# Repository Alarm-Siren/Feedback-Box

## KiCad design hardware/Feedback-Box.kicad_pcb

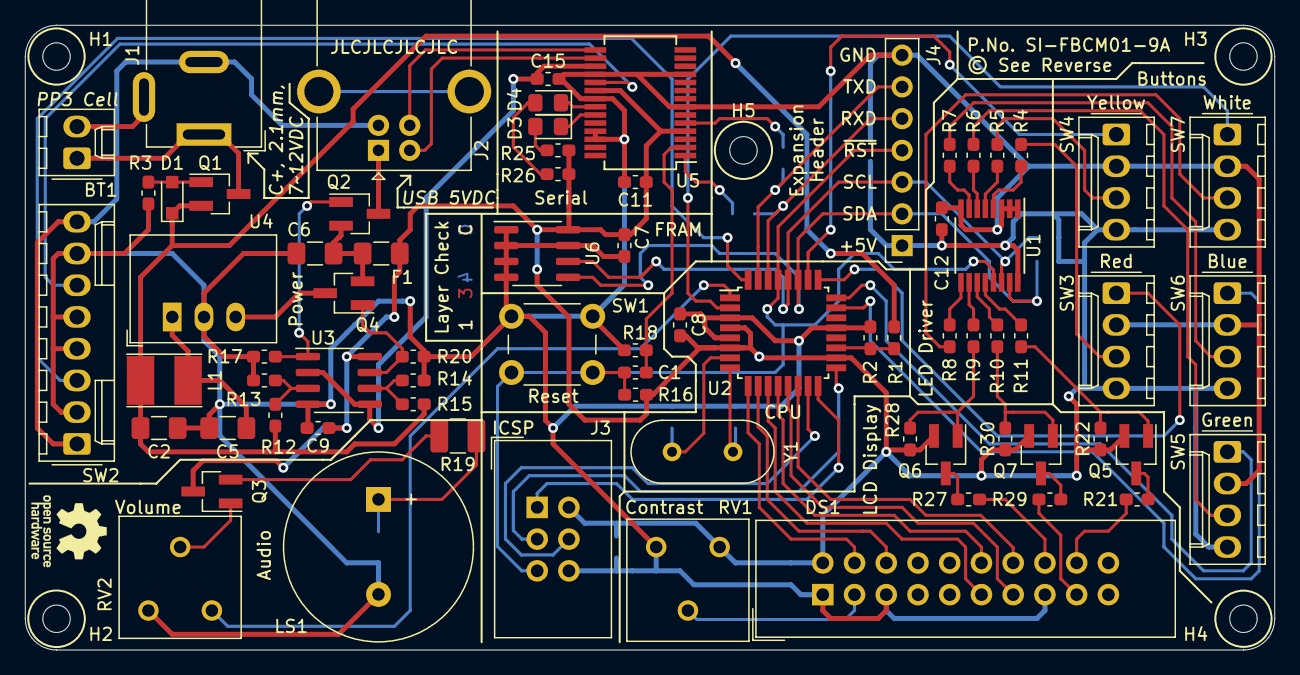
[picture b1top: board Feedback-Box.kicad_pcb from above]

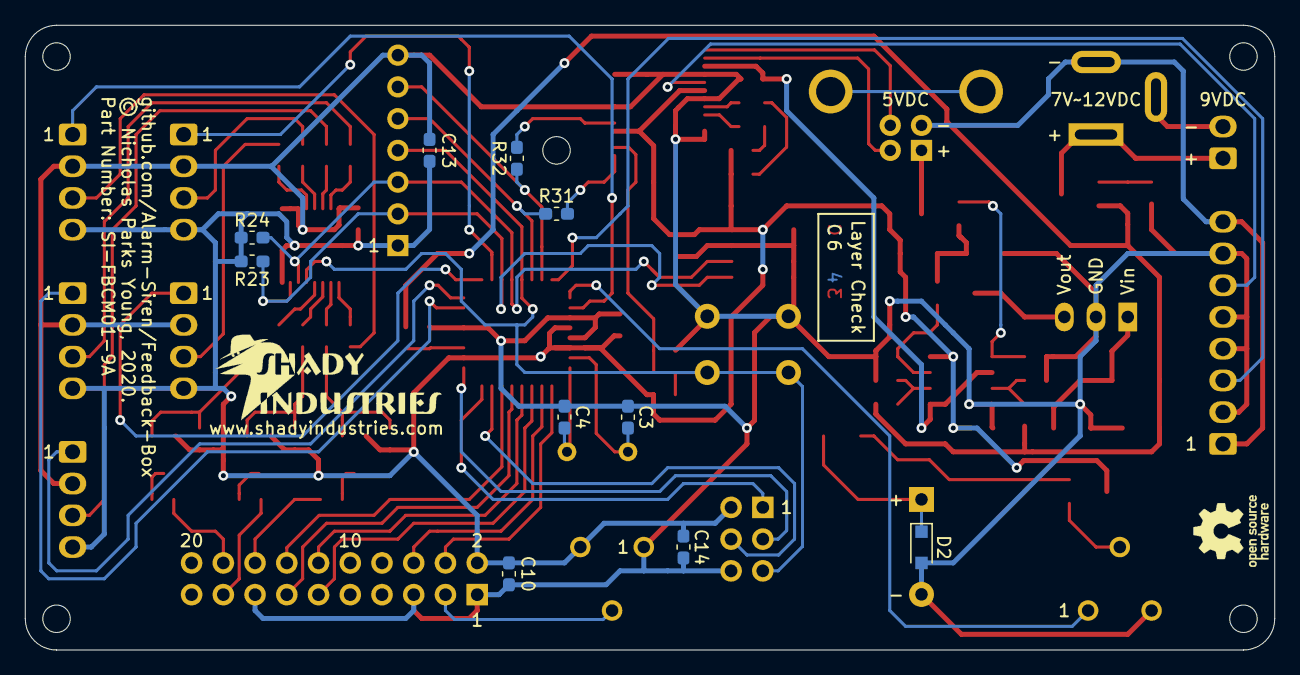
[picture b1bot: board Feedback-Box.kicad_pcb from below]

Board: 2 copper layers, 100.0 x 50.0 mm, 91 parts (12 on the bottom side), 76 nets.

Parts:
BT1: BX0023; Molex_KK-254_AE-6410-02A_1x02_P2.54mm_Vertical
C1, C7, C8, C9, C10, C11, C12, C13, C14, C15: 100n; C_0603_1608Metric_Pad1.05x0.95mm_HandSolder
C2, C6: 10u; C_1206_3216Metric_Pad1.42x1.75mm_HandSolder
C3, C4: 22p; C_0603_1608Metric_Pad1.05x0.95mm_HandSolder
C5: 4.7u; C_1206_3216Metric_Pad1.42x1.75mm_HandSolder
D1: MM3Z7V5ST1G; D_SOD-323_HandSoldering
D2: SS16HE; D_SOD-323_HandSoldering
D3: LTST-C171KRKT; LED_0805_2012Metric_Pad1.15x1.40mm_HandSolder
D4: LTSTS-C171KGKT; LED_0805_2012Metric_Pad1.15x1.40mm_HandSolder
DS1: NHD-0216K1Z-FS(RGB)-FBW-REV1; IDC-Header_2x10_P2.54mm_Vertical
F1: 0ZCJ0025AF2E; Fuse_1206_3216Metric_Pad1.42x1.75mm_HandSolder
G1: LOGO; SI-Logo-W20.3mm_H8.4mm
G2, G3: OSHW-Logo_5.7x6mm_SilkScreen
H1, H2, H3, H4, H5: MountingHole_2.2mm_M2
J1: 694106301002; BarrelJack_Wuerth_6941xx301002
J2: UJ2-BH-1-TH; USB_B_OST_USB-B1HSxx_Horizontal
J3: T821106A1S100CEU; IDC-Header_2x03_P2.54mm_Vertical
J4: SSW-107-01-T-S; PinSocket_1x07_P2.54mm_Vertical
L1: 12u; L_Taiyo-Yuden_NR-40xx_HandSoldering
LS1: CVS-1508; Buzzer_15x7.5RM7.6
Q1, Q2, Q4, Q5, Q6, Q7: FDN340P; SOT-23_Handsoldering
Q3: MMBT2222ALT1G; SOT-23_Handsoldering
R1: 8.2k; R_0603_1608Metric_Pad1.05x0.95mm_HandSolder
R2: 4.7k; R_0603_1608Metric_Pad1.05x0.95mm_HandSolder
R3, R13, R15: 100k; R_0603_1608Metric_Pad1.05x0.95mm_HandSolder
R4, R5, R6, R7, R8, R21, R29: 120; R_0603_1608Metric_Pad1.05x0.95mm_HandSolder
R9, R10, R11: 0; R_0603_1608Metric_Pad1.05x0.95mm_HandSolder
R12, R17, R20, R22, R28, R30: 68k; R_0603_1608Metric_Pad1.05x0.95mm_HandSolder
R14: 82k; R_0603_1608Metric_Pad1.05x0.95mm_HandSolder
R16: 10k; R_0603_1608Metric_Pad1.05x0.95mm_HandSolder
R18, R25, R26, R31, R32: 1k; R_0603_1608Metric_Pad1.05x0.95mm_HandSolder
R19: 62; R_1210_3225Metric_Pad1.42x2.65mm_HandSolder
R23, R24: 3.3k; R_0603_1608Metric_Pad1.05x0.95mm_HandSolder
R27: 150; R_0603_1608Metric_Pad1.05x0.95mm_HandSolder
RV1, RV2: 10k; Potentiometer_Bourns_3386F_Vertical
SW1: B3W-1000; SW_PUSH_6mm
SW2: Y200AA2C203NQ; Molex_KK-254_AE-6410-08A_1x08_P2.54mm_Vertical
SW3: EG Starts Red; Molex_KK-254_AE-6410-04A_1x04_P2.54mm_Vertical
SW4: EG Starts Yellow; Molex_KK-254_AE-6410-04A_1x04_P2.54mm_Vertical
SW5: EG Starts Green; Molex_KK-254_AE-6410-04A_1x04_P2.54mm_Vertical
SW6: EG Starts Blue; Molex_KK-254_AE-6410-04A_1x04_P2.54mm_Vertical
SW7: EG Starts White; Molex_KK-254_AE-6410-04A_1x04_P2.54mm_Vertical
U1: TLC59208FIPWR; TSSOP-16_4.4x5mm_P0.65mm
U2: ATmega328P-AU; TQFP-32_7x7mm_P0.8mm
U3: LMV358IDR; SOIC-8_3.9x4.9mm_P1.27mm
U4: R-78E5.0-0.5; Converter_DCDC_RECOM_R-78E-0.5_THT
U5: FT232RL; SSOP-28_5.3x10.2mm_P0.65mm
U6: FM24C16B; SOIC-8_3.9x4.9mm_P1.27mm
Y1: 16MHz; Crystal_HC49-4H_Vertical

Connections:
+3V3: C15.1, U3.2, U3.5, U5.17
+5V: C7.1, C8.1, C9.1, C10.1, C11.1, C12.1, C13.1, C14.1, DS1.2, F1.1, J3.2, J4.1, Q3.3, Q5.2, Q6.2, Q7.2, R16.2, R22.2, R23.2, R24.2, R25.1, R26.1, R28.2, R30.2, RV1.3, SW3.4, SW4.4, SW5.4, SW6.4, SW7.4, U1.16, U2.4, U2.6, U2.18, U3.8, U5.4, U5.20, U6.8
/MISO: J3.1, U2.16
/MOSI: J3.4, U2.15
/SCLK: J3.3, U2.17
/XTAL1: C3.2, U2.7, Y1.1
/XTAL2: C4.2, U2.8, Y1.2
/~RXLED: D4.1, U5.22
/~TXLED: D3.1, U5.23
BAT: C2.1, D1.1, L1.1, Q1.2, R1.2, R12.2, R14.2
BTN1: SW3.1, U2.25
BTN2: SW4.1, U2.26
BTN3: SW5.1, U2.24
BTN4: SW6.1, U2.23
BTN5: SW7.1, U2.2
GND: C2.2, C3.1, C4.1, C5.2, C6.2, C7.2, C8.2, C9.2, C10.2, C11.2, C12.2, C13.2, C14.2, C15.2, D2.2, DS1.1, DS1.5, DS1.15, J3.6, J4.7, LS1.2, R2.1, R3.1, R13.1, R15.1, R17.1, R18.1, R20.1, RV1.1, RV2.3, SW1.2, SW2.2, SW2.4, SW2.5, SW2.7, SW3.2, SW4.2, SW5.2, SW6.2, SW7.2, U1.1, U1.2, U1.3, U1.8, U2.3, U2.5, U2.21, U3.4, U4.2, U5.7, U5.11, U5.18, U5.21, U5.25, U5.26, U6.1, U6.2, U6.3, U6.4, U6.7
GNDS: J1.2, J2.4, SW2.1, SW2.8
LCD_D4: DS1.11, U2.11
LCD_D5: DS1.12, U2.12
LCD_D6: DS1.13, U2.13
LCD_D7: DS1.14, U2.14
LCD_E: DS1.6, U2.10
LCD_RS: DS1.4, U2.9
LED1: R4.1, SW3.3
LED2: R5.1, SW4.3
LED3: R6.1, SW5.3
LED4: R7.1, SW6.3
LED5: R8.1, SW7.3
unnamed: BT1.1, J1.1, Q1.3
unnamed: BT1.2, J1.3
unnamed: C5.1, L1.2, U4.1
unnamed: C6.1, F1.2, Q2.2, Q4.2
unnamed: D1.2, Q1.1, R3.2
unnamed: D2.1, LS1.1, R19.1
unnamed: D3.2, R25.2
unnamed: D4.2, R26.2
unnamed: DS1.3, RV1.2
unnamed: J2.1, Q2.3
unnamed: Q2.1, R17.2, U3.1
unnamed: Q3.1, RV2.2
unnamed: Q3.2, R19.2
unnamed: Q4.1, R20.2, U3.7
unnamed: Q4.3, U4.3
unnamed: Q5.3, R21.1
unnamed: Q6.3, R27.1
unnamed: Q7.3, R29.1
unnamed: R1.1, R2.2, U2.19
unnamed: R4.2, U1.4
unnamed: R5.2, U1.5
unnamed: R6.2, U1.6
unnamed: R7.2, U1.7
unnamed: R8.2, U1.9
unnamed: R9.2, U1.10
unnamed: R10.2, U1.11
unnamed: R11.2, U1.12
unnamed: R12.1, R13.2, U3.3
unnamed: R14.1, R15.2, U3.6
unnamed: R31.2, U5.1
unnamed: R32.2, U5.5
PROG~EN: SW2.3, U2.32
RXD: J4.5, R31.1, U2.30
SCL: J4.3, R24.1, U1.14, U2.28, U6.6
SCR_B+: DS1.18, R21.2
SCR_B-: Q5.1, R11.1, R22.1
SCR_G+: DS1.17, R29.2
SCR_G-: Q7.1, R10.1, R30.1
SCR_R+: DS1.16, R27.2
SCR_R-: Q6.1, R9.1, R28.1
SDA: J4.2, R23.1, U1.15, U2.27, U6.5
SPK: RV2.1, U2.1
TXD: J4.6, R32.1, U2.31
USBD+: J2.3, U5.15
USBD-: J2.2, U5.16
USB~RST: SW2.6, U5.19
~DTR: C1.1, R18.2, U5.2
~RST: C1.2, J3.5, J4.4, R16.1, SW1.1, U1.13, U2.29

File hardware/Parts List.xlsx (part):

Reference | Manufacturer | Mft's Part Number | Qty/unit | Total Qty | Price/each (£) | Subtotal (£) | Mouser Part No | Farnell Part No | Misc. Part Link | Footprint | Description
BT1 | Bulgin | BX0023 | 1 | 5 | 4.4800000000000004 | 22.400000000000002 | 122-BX0023 | 1184193 |  | n/a | PP3 (9V) battery holder, panel-mount, black, Flying Leads
BT1a | Molex | 22292021 | 1 | 5 | 0.32800000000000001 | 1.6400000000000001 | 538-22-29-2021 | 1360130 |  | Connector_Molex:Molex_KK-254_AE-6410-02A_1x02_P2.54mm_Vertical | Molex KK 254 Series, 2pin header, Wire-to-board, THT
BT1b | Molex | 22013027 | 1 | 5 | 6.4199999999999993E-2 | 0.32099999999999995 | 538-22-01-3027 | 1462825 |  | n/a | Molex KK Connector Housing 2pin w/Mating flange & polarizing ribs
BT1c, SW2c | Molex | 08520123 | 44 | 220 | 1.8100000000000002E-2 | 3.9820000000000002 | 538-08-52-0101-CT | 2888993 |  | n/a | Molex KK Crimp Contacts, 30-22AWG, Phospher Bronze, Cut Strip
C1, C7-C15 | Wurth Elektronik | 885012206071 | 10 | 50 | 2.8000000000000001E-2 | 1.4000000000000001 | 710-885012206071 | 2495173 |  | Capacitor_SMD:C_0603_1608Metric_Pad1.05x0.95mm_HandSolder | Capacitor MLCC 100nF, X7R, 25V, +/-10%, SMD 0603
C2, C6 | Taiyo Yuden | UMK316BBJ106KL-T | 2 | 10 | 0.13900000000000001 | 1.3900000000000001 | 963-UMK316BBJ106KL-T |  |  | Capacitor_SMD:C_1206_3216Metric_Pad1.42x1.75mm_HandSolder | Capacitor MLCC 10uF, X5R, 50V, +/-10%, SMD 1206
C3, C4 | AVX | 06035C220JAT2A | 2 | 10 | 6.6000000000000003E-2 | 0.66 | 581-06035C220JAT2A | 2332643 |  | Capacitor_SMD:C_0603_1608Metric_Pad1.05x0.95mm_HandSolder | Capacitor MLCC 22pF, X7R, 50V, +/-5%, SMD 0603
C5 | Taiyo Yuden | UMK316AB7475KL-T | 1 | 5 | 0.24 | 1.2 | 963-UMK316AB7475KL-T |  |  | Capacitor_SMD:C_1206_3216Metric_Pad1.42x1.75mm_HandSolder | Capacitor MLCC 4.7uF, X7R, 50V, +/-10%, SMD 1206
D1 | ON Semiconductor | MM3Z7V5ST1G | 1 | 5 | 9.2999999999999999E-2 | 0.46499999999999997 | 863-MM3Z7V5ST1G | 2441322 |  | Diode_SMD:D_SOD-323_HandSoldering | Single Zener Diode, 7.5V, 300mW, SMD SOD-323
D2 | ON Semiconductor / Fairchild | SS16HE | 1 | 5 | 7.6999999999999999E-2 | 0.38500000000000001 | 512-SS16HE | 2822565 |  | Diode_SMD:D_SOD-323_HandSoldering | Schottky Rectifier Diode, Vmax=60V, Imax=1A, Vf=680mV, SMD SOD-323
D3 | Lite-On | LTST-C171KRKT | 1 | 5 | 0.217 | 1.085 | 859-LTST-C171KRKT |  |  | LED_SMD:LED_0805_2012Metric_Pad1.15x1.40mm_HandSolder | Standard Red LED, 55mCD, SMD 0805
D4 | Lite-On | LTST-C171KGKT | 1 | 5 | 0.217 | 1.085 | 859-LTST-C171KGKT |  |  | LED_SMD:LED_0805_2012Metric_Pad1.15x1.40mm_HandSolder | Standard Green LED, 55mCD, SMD 0805
DS1 | Newhaven Displays | NHD-0216K1Z-FS(RGB)-FBW-REV1 | 1 | 5 | 10.55 | 52.75 | 763-0216K1Z-FS-FBWR1 |  |  | n/a | Character LCD 16x2, RGB Backlight, Parallel access, THT
DS1a | Amphenol | T821120A1S100CEU | 1 | 5 | 0.248 | 1.24 |  | 2215309 |  | Connector_IDC:IDC-Header_2x10_P2.54mm_Vertical | IDC Socket 2.54mm pitch, 2x10, Vertical, THT
DS1b | Amphenol | T812120A100CEU | 1 | 5 | 0.23 | 1.1500000000000001 |  | 2215236 |  | n/a | IDC Plug 2.54mm pitch, 2x10, Vertical
DS1c, SW2a | Molex | 22272081 | 2 | 10 | 0.33700000000000002 | 3.37 | 538-22-27-2081 | 9731180 |  | Connector_Molex:Molex_KK-254_AE-6410-08A_1x08_P2.54mm_Vertical | Molex KK 254 Series, 8pin header, Wire-to-board, THT
DS1d, SW2b | Molex | 22013087 | 2 | 10 | 0.20599999999999999 | 2.06 | 538-22-01-3087 | 2396394 |  | n/a | Molex KK Connector Housing 8pin w/Mating flange & polarizing ribs
DS1e | Molex | 22272061 | 1 | 5 | 0.33 | 1.6500000000000001 | 538-22-27-2061 | 9731172 |  | n/a | Molex KK 254 Series, 6pin header, Wire-to-board, THT
DS1f | Molex | 22013067 | 1 | 5 | 0.192 | 0.96 | 538-22-01-3067 | 1654529 |  | n/a | Molex KK Connector Housing 6pin w/Mating flange & polarizing ribs
F1 | Bel Fuse | 0ZCJ0025AF2E | 1 | 5 | 8.5000000000000006E-2 | 0.42500000000000004 | 530-0ZCJ0025AF2E | 2834884 |  | Fuse:Fuse_1206_3216Metric_Pad1.42x1.75mm_HandSolder | PTC Resettable Fuse, Hold 250mA, Trip 500mA, 24VDC, SMD 1206
J1 | Wurth Elektronik | 694106301002 | 1 | 5 | 0.70099999999999996 | 3.5049999999999999 | 710-694106301002 | 2472149 |  | Connector_BarrelJack:BarrelJack_Wuerth_6941xx301002 | Barrel Jack Socket, ID 2.1mm, OD 5.5mm, THT
J2 | CUI Devices | UJ2-BH-1-TH | 1 | 5 | 0.41799999999999998 | 2.09 | 490-UJ2-BH-1-TH |  |  | Connector_USB:USB_B_OST_USB-B1HSxx_Horizontal | USB-B Socket, THT
J3 | Amphenol | T821106A1S100CEU | 1 | 5 | 0.19900000000000001 | 0.99500000000000011 |  | 2215302 |  | Connector_IDC:IDC-Header_2x03_P2.54mm_Vertical | IDC Socket 2.54mm pitch, 2x3, Vertical, THT
J4 | Samtec | SSW-107-01-T-S | 1 | 5 | 0.73499999999999999 | 3.6749999999999998 | 200-SSW10701TS | 2667434 |  | Connector_PinSocket_2.54mm:PinSocket_1x07_P2.54mm_Vertical | 1x07 2.54mm Square Header Recepticle, Vertical, THT
L1 | RECOM | RLS-126 | 1 | 5 | 0.46800000000000003 | 2.3400000000000003 | 919-RLS-126 |  |  | Inductor_SMD:L_Taiyo-Yuden_NR-40xx_HandSoldering | 12uH 0.8A Fixed Inductor, SMD
LS1 | CUI Devices | CVS-1508 | 1 | 5 | 2.29 | 11.45 | 490-CVS-1508 |  |  | Buzzer_Beeper:Buzzer_15x7.5RM7.6 | Loudspeaker, 300mW 8R, D15mm, THT
Q1-Q2, Q4-Q7 | ON Semiconductor / Fairchild | FDN340P | 6 | 30 | 0.25600000000000001 | 7.68 | 512-FDN340P | 9846310 |  | Package_TO_SOT_SMD:SOT-23_Handsoldering | Mosfet Transistor, P-Channel, 2A, 20V, 0.06R, SMD SOT-23
Q3 | ON Semiconductor | MMBT2222ALT1G | 1 | 5 | 0.10100000000000001 | 0.505 | 863-MMBT2222ALT1G | 1459098 |  | Package_TO_SOT_SMD:SOT-23_Handsoldering | Bipolar Transistor, NPN, 40V, 300MHz, 225mW, 600mA, SMD SOT-23
R1 | Yageo | RC0603FR-078K2L | 1 | 5 | 1.4E-2 | 7.0000000000000007E-2 | 603-RC0603FR-078K2L | 9238590 |  | Resistor_SMD:R_0603_1608Metric_Pad1.05x0.95mm_HandSolder | Resistor 8.2kR, 100mW, 75V, +/-1%, SMD 0603
R12, R17, R20, R22, R28, R30 | Yageo | RC0603FR-0768KL | 6 | 30 | 1.4E-2 | 0.42 | 603-RC0603FR-0768KL | 9238700 |  | Resistor_SMD:R_0603_1608Metric_Pad1.05x0.95mm_HandSolder | Resistor 68kR, 100mW, 75V, +/-1%, SMD 0603
R14 | Yageo | RC0603FR-0782KL | 1 | 5 | 1.4E-2 | 7.0000000000000007E-2 | 603-RC0603FR-0782KL | 9238719 |  | Resistor_SMD:R_0603_1608Metric_Pad1.05x0.95mm_HandSolder | Resistor 82kR, 100mW, 75V, +/-1%, SMD 0603
R16 | Yageo | RC0603FR-0710KL | 1 | 5 | 1.4E-2 | 7.0000000000000007E-2 | 603-RC0603FR-0710KL | 9238603 |  | Resistor_SMD:R_0603_1608Metric_Pad1.05x0.95mm_HandSolder | Resistor 10kR, 100mW, 75V, +/-1%, SMD 0603
R18, R25-R26, R31-R32 | Yageo | RC0603FR-071KL | 5 | 25 | 1.4E-2 | 0.35000000000000003 | 603-RC0603FR-071KL | 9238484 |  | Resistor_SMD:R_0603_1608Metric_Pad1.05x0.95mm_HandSolder | Resistor 1kR, 100mW, 75V, +/-1%, SMD 0603
R19 | Yageo | RC1210FR-0762RL | 1 | 5 | 0.122 | 0.61 | 603-RC1210FR-0762RL |  |  | Resistor_SMD:R_1210_3225Metric_Pad1.42x2.65mm_HandSolder | Resistor 62R, 500mW, 75V, +/-1%, SMD 1210
R2 | Yageo | RC0603FR-074K7L | 1 | 5 | 1.4E-2 | 7.0000000000000007E-2 | 603-RC0603FR-074K7L | 9238565 |  | Resistor_SMD:R_0603_1608Metric_Pad1.05x0.95mm_HandSolder | Resistor 4.7kR, 100mW, 75V, +/-1%, SMD 0603
R23, R24 | Yageo | RC0603FR-073K3L | 2 | 10 | 1.4E-2 | 0.14000000000000001 | 603-RC0603FR-073K3L | 9238549 |  | Resistor_SMD:R_0603_1608Metric_Pad1.05x0.95mm_HandSolder | Resistor 3.3kR, 100mW, 75V, +/-1%, SMD 0603
R27 | Yageo | RC0603FR-07150RL | 1 | 5 | 1.4E-2 | 7.0000000000000007E-2 | 603-RC0603FR-07150RL | 9238387 |  | Resistor_SMD:R_0603_1608Metric_Pad1.05x0.95mm_HandSolder | Resistor 150R, 100mW, 75V, +/-1%, SMD 0603
R3, R13, R15 | Yageo | RC0603FR-07100KL | 3 | 15 | 1.4E-2 | 0.21 | 603-RC0603FR-07100KL | 9238727 |  | Resistor_SMD:R_0603_1608Metric_Pad1.05x0.95mm_HandSolder | Resistor 100kR, 100mW, 75V, +/-1%, SMD 0603
R4-R8, R21, R29 | Yageo | RC0603FR-07120RL | 7 | 35 | 1.4E-2 | 0.49 | 603-RC0603FR-07120RL | 9238379 |  | Resistor_SMD:R_0603_1608Metric_Pad1.05x0.95mm_HandSolder | Resistor 120R, 100mW, 75V, +/-1%, SMD 0603
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
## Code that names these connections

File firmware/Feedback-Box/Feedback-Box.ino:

#include <Wire.h>
#include <LiquidCrystal.h>

const byte LED_ADDR = 0x20;
const byte LED_PWM_VAL = 0xFF;
const byte LED_PWM_OFF = 0x00;

const byte LCD_RS = 5;
const byte LCD_EN = 6;
const byte LCD_D4 = 7;
const byte LCD_D5 = 8;
const byte LCD_D6 = 9;
const byte LCD_D7 = 10;

const byte BUTTON_RED = A2;
const byte BUTTON_YEL = A3;
const byte BUTTON_GRN = A1;
const byte BUTTON_BLU = A0;
const byte BUTTON_WHT = 4;
const byte PROG_EN = 2;

const byte BAT_MON = A6;

const byte FRAM_ADDR = 0x50;

const byte SPK_OUT = 3;
const unsigned int NOTE_SUSTAIN = 75;
const unsigned int NOTE_A5 = 880;
const unsigned int NOTE_B5 = 988;
const unsigned int NOTE_C5 = 523;
const unsigned int NOTE_D5 = 587;
const unsigned int NOTE_D5S = 622;
const unsigned int NOTE_E5 = 659;
const unsigned int NOTE_G4 = 392;
const unsigned int NOTE_C4 = 256;
const unsigned int NOTE_D3S = 155;
const unsigned int NOTE_A4S = 459;
const unsigned int NOTE_C5S = 554;


LiquidCrystal lcd(LCD_RS, LCD_EN, LCD_D4, LCD_D5, LCD_D6, LCD_D7);

void setup() {
  // put your setup code here, to run once:
  Wire.begin();

    Wire.beginTransmission(LED_ADDR);
    Wire.write(0x80); // Control: Auto-Increment on All Registers
    Wire.write(0x80); // 00h: MODE1
    Wire.write(0x0b); // 01h: MODE2
    Wire.write(0x00); // 02h: PWM0
    Wire.write(0x00); // 03h: PWM1
    Wire.write(0x00); // 04h: PWM2
    Wire.write(0x00); // 05h: PWM3
    Wire.write(0x00); // 06h: PWM4
    Wire.write(0x00); // 07h: PWM5
    Wire.write(0x00); // 08h: PWM6
    Wire.write(0x00); // 09h: PWM7
    Wire.write(0xFF); // 0Ah: GRPPWM
    Wire.write(0x00); // 0Bh: GRPFREQ
    Wire.write(0xAA); // 0Ch: LEDOUT0
    Wire.write(0xAA); // 0Dh: LEDOUT1
    Wire.write(0x92); // 0Eh: SUBADR1
    Wire.write(0x94); // 0Fh: SUBADR2
    Wire.write(0x98); // 10h: SUBADR3
    Wire.write(0xD0); // 11h: ALLCALLADR
    Wire.endTransmission();

  lcd.begin(16, 2);
  lcd.print("SIFBCM01-8A/0002");

  pinMode(BUTTON_RED, INPUT_PULLUP);
  pinMode(BUTTON_GRN, INPUT_PULLUP);
  pinMode(BUTTON_YEL, INPUT_PULLUP);
  pinMode(BUTTON_BLU, INPUT_PULLUP);
  pinMode(BUTTON_WHT, INPUT_PULLUP);
  pinMode(PROG_EN, INPUT_PULLUP);
  pinMode(SPK_OUT, OUTPUT);
    
}

static byte x = 0;
static byte mode = 0;

void loop() {
  // put your main code here, to run repeatedly:

    if (!digitalRead(BUTTON_WHT) && !digitalRead(BUTTON_GRN)) {
      mode++;
      if (mode > 2) {
        mode = 0;
      }
    }
    
    Wire.beginTransmission(LED_ADDR);
    Wire.write(0xA2);
    x = x + 1;
    for (int i=0; i<8; i++) {

      if (mode == 2)
      {
        Wire.write(x);
      } 
      else
      {
        if (bitRead(x, i))
        {
          Wire.write(LED_PWM_VAL);
        }
        else
        {
          if (mode == 0) {
            Wire.write(LED_PWM_OFF);
          } else {
            Wire.write(LED_PWM_VAL);
          }
        }
      }
    }
    Wire.endTransmission();

    lcd.setCursor(0, 1);
    lcd.print("                ");
    lcd.setCursor(0, 1);
    if (!digitalRead(BUTTON_RED)) lcd.print("R");
    if (!digitalRead(BUTTON_YEL)) lcd.print("Y");
    if (!digitalRead(BUTTON_GRN)) lcd.print("G");
    if (!digitalRead(BUTTON_BLU)) lcd.print("B");
    if (!digitalRead(BUTTON_WHT)) lcd.print("W");
    if (!digitalRead(PROG_EN)) lcd.print("P");
    lcd.setCursor(7, 1);
    lcd.print(x);
    lcd.setCursor(11, 1);
    lcd.print(analogRead(BAT_MON));
    lcd.setCursor(15, 1);
    lcd.print(mode);

  if (!digitalRead(BUTTON_WHT) && !digitalRead(BUTTON_YEL)) {
    delay(200);
    
    tone(SPK_OUT,2093); //C7
    delay(100);
    
    noTone(SPK_OUT);
    delay(50);
    
    tone(SPK_OUT,3520);  //A7
    delay(200);
    
    noTone(SPK_OUT);
  }

    
  
    
    delay(100);
}

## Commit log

2020-02-08 Upload initial schematic
2020-02-09 Started on Hardware Layout
    Power & Loudspeaker sections done. Provisional layout of USB and most connectors also done.
2020-02-09 Labelled up the Power/Audio, routed a bit more power
2020-02-10 Mostly finished layout, just needs a little final routing
2020-02-10 Moved "buttons" SS text
2020-02-12 Finish Layout
    Finished PCB layout;
    Also added another decoupling cap for the ICSP;
    Also added (C) info to schematic + layout;
    Also added Chris' name as "checked by".
2020-02-14 Added RST+TX+RX to Expansion Header
    Added RST, and Serial TXD/RXD to the Expansion header. To allow TXD/RXD from the FT232RL to be safely 'overriden' by an expansion device, two additional 1K resistors have been fitted as well.
2020-02-15 Generate gerbers for production
2020-02-23 Correction to Parts List, Starting on Interface Program
    Interface Program now has ability to detect the addition and removal of individual USB Serial devices, and detect their COM Port number and Serial Numbers
2020-02-25 Layout revision 8B
    Fixed misplaced Pin 1 locator on rear silkscreen for part J4
2020-03-13 Update to hardware revision 6C
    Made the drill sizes for the Variable Resistors bigger, because the previous sizes where only *just* big enough.
2020-03-18 Some very basic firmware to start checking hardware
2020-08-21 Switch R19 to 1210, 62R resistor
    This allows the speaker to run at 0.35W instead of the previous 0.11W.

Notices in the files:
hardware/Feedback-Box.kicad_pcb:
© Nicholas Parks Young, 2020. Some Rights Reserved.
© See Reverse
